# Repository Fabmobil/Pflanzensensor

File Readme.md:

#  Pflanzensensor

Dies ist das Repository mit dem Quellcode und allen Informationen zum Fabmobil Pflanzensensor. Weiterführende Erklärungen sind im [Wiki](https://github.com/Fabmobil/Pflanzensensor/wiki) zu finden.

**Firmware flashen ohne Programmierumgebung:** im Browser per USB über den
[Webflasher](https://fabmobil.github.io/Pflanzensensor/) (Chrome, Edge oder Opera am Computer).

| Verzeichnis | Inhalt |
| --- | --- |
| [`firmware/`](firmware) | Quellcode der Firmware 3 (PlatformIO, ESP8266 und ESP32), Weboberfläche, Tests – Bauen und Entwickeln siehe [firmware/README.md](firmware/README.md) |
| [`webflasher/`](webflasher) | Seite zum Flashen per USB im Browser (GitHub Pages) |
| [`Dokumentation/`](Dokumentation) | Datenblätter, Schaltpläne, Pinouts, 3D-Modelle, Workshop-Unterlagen |

Im [Wiki](https://github.com/Fabmobil/Pflanzensensor/wiki) gibt es weiterführende Informationen und Anleitungen.

wird gefördert von:

und unterstützt von:

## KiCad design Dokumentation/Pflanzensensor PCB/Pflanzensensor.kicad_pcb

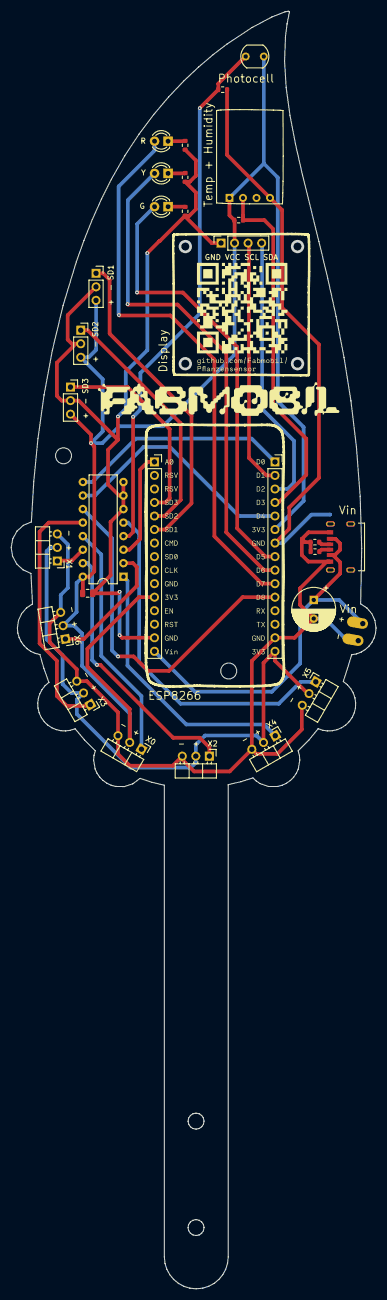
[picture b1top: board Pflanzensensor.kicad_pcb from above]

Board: 2 copper layers, 68.5 x 239.9 mm, 32 parts (0 on the bottom side), 32 nets.

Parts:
+: Conn_01x01; SolderWirePad_1x01_SMD_1x2mm
-: SolderWirePad_1x01_SMD_1x2mm
C1: C_Polarized; CP_Radial_D8.0mm_P3.50mm
C2: 0.1 µF; C_0805_2012Metric
DH1: Conn_01x04; PinSocket_1x04_P2.54mm_Vertical
DHT11: VCC SIG – GND; Aosong_DHT11_5.5x12.0_P2.54mm
ESP1, ESP2: Conn_01x15; PinSocket_1x15_P2.54mm_Vertical
IC1: CD4051B; DIP-16_W7.62mm
LEDG1: Green 568nm; LED_D3.0mm
LEDR1: Red 617nm; LED_D3.0mm
LEDY1: 588nm; LED_D3.0mm
PHR1: R_Photo; R_LDR_5.1x4.3mm_P3.4mm_Vertical
R1: 1KΩ; R_0603_1608Metric
R2: 10KΩ; R_0603_1608Metric
R5, R6: 5K1; R_0603_1608Metric
RG1: 56Ω; R_0603_1608Metric
RR1: 68Ω; R_0603_1608Metric
RY1: 62Ω; R_0603_1608Metric
SD1, SD2, SD3: Conn_01x03; PinSocket_1x03_P2.54mm_Vertical
Vin: GCT_USB4125-GF-A-0190_REVA2
X0, X1, X2, X3, X4, X5, X6: Conn_01x03; PinHeader_1x03_P2.54mm_Horizontal
gndpad: SolderWirePad_1x01_SMD_1x2mm

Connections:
unnamed: +.1, C1.1, ESP1.15 (Vin), Vin.A9, Vin.B9
unnamed: -.1, C1.2, ESP2.14 (GND), R5.2, R6.2, Vin.A12, Vin.B12, X0.3, X1.3, X2.3, X3.3, X4.3, X5.3, X6.3
unnamed: C2.1, DH1.1 (GND), ESP1.14 (GND), IC1.6 (INH), IC1.7 (VEE), IC1.8 (VSS), RG1.2, RR1.2, RY1.2, SD1.2, SD2.2, SD3.2
unnamed: DH1.3 (SCL), ESP2.2 (D1)
unnamed: DH1.4 (SDA), ESP2.3 (D2)
unnamed: C2.2, DH1.2 (VCC), DHT11.1 (VCC), ESP1.11 (3V3), ESP2.6 (GND), IC1.16 (VDD), PHR1.1, R2.1, SD1.3, SD2.3, SD3.3, X0.2, X6.2
unnamed: DHT11.4 (GND), ESP2.7 (3V3), R1.1, gndpad.1
unnamed: DHT11.2 (IO), ESP2.4 (D3), R2.2
unnamed: ESP1.1 (A0), IC1.3 (X)
unnamed: ESP1.6 (SD1), SD1.1
unnamed: ESP1.5 (SD2), SD2.1
unnamed: ESP1.4 (SD3), SD3.1
unnamed: ESP2.1 (D0), IC1.9 (C)
unnamed: ESP2.5 (D4), IC1.10 (B)
unnamed: ESP2.8 (D5), LEDG1.2 (A)
unnamed: ESP2.9 (D6), LEDY1.2 (A)
unnamed: ESP2.10 (D7), LEDR1.2 (A)
unnamed: ESP2.11 (D8), IC1.11 (A)
unnamed: IC1.13 (X0), X0.1
unnamed: IC1.14 (X1), X1.1
unnamed: IC1.15 (X2), X2.1
unnamed: IC1.12 (X3), X3.1
unnamed: IC1.1 (X4), X4.1
unnamed: IC1.5 (X5), X5.1
unnamed: IC1.2 (X6), X6.1
unnamed: IC1.4 (X7), PHR1.2, R1.2
unnamed: ESP2.15 (3V3), X1.2, X2.2, X3.2, X4.2, X5.2
unnamed: LEDG1.1 (K), RG1.1
unnamed: LEDR1.1 (K), RR1.1
unnamed: LEDY1.1 (K), RY1.1
unnamed: R5.1, Vin.A5
unnamed: R6.1, Vin.B5

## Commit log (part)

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2024-08-11 Debugausgabe umgebaut
2024-08-11 Variablenreset gefixt.
2024-08-12 Webhook mit Ping aller X Stunden
2024-08-12 Refactoting
2024-08-12 bugfix
2024-08-12 Version 0.6
2024-08-12 Verbesserung am CSS
2024-08-12 Kommentierung verbessert.
2024-08-12 Anpassen der Reihenfolge der Schwellwerte auf der Adminseite
2024-08-13 Refactoring LEDAmpel Modul
2024-08-14 Produktiondaten + Doku Pflanzensensor_V3
    Die Files aus den Ordnern Assembly und Gerber sind die Produktionsdaten inkl. Stückliste, die der Hersteller für die 100 Stück Bestellung bekommen hat. Die Kicad File ist der aktuelle Stand (August 2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
2024-08-19 passende make.com Vorlagen für neue WebhookSendeInit()-Funktion
2024-08-19 Bugfix für Neustartcount bei WebhookInit
2024-08-21 Update Webhook Logik
2024-08-21 Version bump 0.7
2024-08-24 Debug wird nicht mehr gebraucht
2024-08-24 Bilder verbessert
2024-08-24 Bugfix Filename
2024-09-04 Analogmesswerte in Adminseite angezeigt; Typos gefixt
2024-09-09 Wifi Accesspoint Passwoerter in passwoerter_Beispiel.h statt Configuration.h
2024-09-09 Umbenennung Configuration.h -> einstellungen.h
2024-09-20 Handout für den 3 Tage Workshop
2024-09-20 eindeutigere Bezeichnung der Minimal- und Maximalwerte der Analgosensoren
2024-09-20 bessere Ausgabe auf serieller Schnittstelle bei nicht funktionierendem Sensor
2024-09-20 Sensor wechselt zu Accesspoint-Modus wenn WIFI Verbindung verloren ist. Nicht aktive Wifidaten sind auf der Adminseite editierbar.
2024-09-20 LED Ampel in Modus 1 aus, wenn kein Sensorwert auf Display angezeigt wird.
2024-09-20 weirder bugfix: DHT_H als Variablenname macht Kompilierfehler.
2024-09-20 LED Ampel auf richtigem Weg ausschalten..
2024-09-20 refactoring von displayanzeige; unnötige variablen entfernt; Versionsbump v1.1.1
2024-09-20 Umschalter für AP und WLAN Modus
2024-09-21 AP settings in Admininterface änderbar
2024-09-21 Versionbump 1.2.0
2024-09-21 Versionbump v1.2.1
2024-09-23 Dateien an dieser Stelle nicht mehr benötigt
2024-09-24 Dokuupdate: Handout 3 Tage
2024-09-30 kein Alert bei deaktiviertem Webhook-Modul auf der Adminseite
2024-09-30 Webhook checkbox wird jetzt auch abgefragt.
2024-09-30 Versionbump V1.2.2
2024-10-03 Adminseite, Variablenspeicher und Bugfixes
2024-10-14 logger statt Serial.print
2024-10-19 mehr Umstrukturierungen
2024-10-19 Versionbump auf 1.3.0
2024-10-20 char statt String: siehe notizen.txt
2024-10-20 Umbenennung der Datei
2024-10-20 bugffix
2024-10-20 wir sparen immer noch ram
2024-10-21 F-Strings zum RAM sparen
2024-10-21 Jedes Byte RAM zählt!
2024-10-21 Logger verbraucht jetzt weniger RAM
2024-10-21 Bugfix für Anzeige der SSIDs
2024-10-21 update Stylesheet
2024-10-21 Versionbump v1.3.1
2024-10-21 Versionbump v1.3.2
2024-10-22 Update Workshopanleitungen
2024-10-22 apAktiv hat gefehlt
2024-10-22 Keine Passwoerter auf DEBUG Seite
2024-10-22 Mehr überarbeitung für Wechsel des WLAN Modus
2024-10-22 Workshopdateien hinzugefügt
2024-10-22 Versionbump v1.3.3
2024-10-22 noch mehr Bugfixes
2024-10-23 housekeeping Skripte
2024-10-23 Die Dateien sollten nie im Repo landen
2024-10-23 gitignore update
2024-10-23 step 1: sensorklasse
2024-10-24 immer akutelle libraries
2024-10-24 update HousekeepingSkripte
2024-10-24 Checkboxüberprüfung überarbeitet
2024-10-24 Versionsbump v1.3.4
2024-11-04 Typo
2024-11-04 labels für ports
2025-09-15 Erste Version der Mailsendefunktion
2025-09-15 added todo
2025-10-15 new ui
2025-10-15 css Vereinfachung
2025-10-15 Logo kleiner
2025-10-15 Version 2.19.0: Neues Admininterface
2025-10-17 Version 2.21.0: Mehr UI Updates, mehr AJAX
2025-10-17 Version 2.22.1: CSS Anpassungen und kleinere Fixes
2025-10-19 Version 2.23.1: kleine Bugfixes und Übersetzungen
2025-10-19 V2.23.3: Min Max Anzeige bei Threshold Slider
2025-10-21 Aufräumen
2025-10-22 V2.24.0: Autocal für Analogsensoren
2025-10-22 clang format über alles
2025-10-22 V2.24.2: fix Display Settings bug
2025-10-22 V2.24.3: Kleinere Bugfixes
2025-10-22 V2.24.5: Aufräumen
2025-10-22 Bugfix Display Sensor
2025-10-22 Update der Dokumentation
2025-10-22 Bild vom Webinterface
2025-10-23 MD5 für Update deaktiviert
2025-10-23 Revise sponsorship section in Readme.md
    Updated sponsorship section with logos and links.
2025-10-23 Initial plan
2025-10-23 Add PreferencesManager class implementation
2025-10-27 Kurzvortrag Mikrocontroller
2025-10-28 Update Dokumentation
2025-11-03 Add Preferences library and refactor configuration persistence
    - Added Preferences library to platformio.ini
    - Created preferences_manager.h/.cpp with namespace-based configuration storage
    - Implemented helper functions for all configuration namespaces (general, WiFi, display, log, LED traffic light, debug, sensors)
    - Updated manager_config_persistence.cpp to use Preferences as primary storage
    - Added migration logic from JSON to Preferences with backup
    - Updated loadFromFile to check Preferences first, then migrate from JSON if needed
2025-11-03 Update DisplayManager to use Preferences for display settings
    - Modified loadConfig() to check Preferences first, then migrate from JSON
    - Modified saveConfig() to write to Preferences
    - Added migration logic from display_config.json to Preferences with backup
    - Sensor-specific display settings kept in separate JSON file for now
    - Added comprehensive German logger messages for display operations
2025-11-03 Final verification and summary of Preferences refactoring
2025-11-03 Update documentation to clarify Preferences storage and current state
    - Documented that Preferences are stored in EEPROM (0x405FB000), separate from LittleFS
    - Clarified that Preferences survive filesystem flashes
    - Listed what is currently in Preferences vs still in JSON (sensors.json)
    - Removed references to automatic JSON migration
    - Noted that analog sensor raw values and autocal settings are NOT yet in Preferences
    - Updated README to reflect current implementation state
2025-11-03 Update sensor atomic update functions to use Preferences (partial)
    - Updated updateSensorThresholdsInternal to use Preferences
    - Updated updateAnalogMinMaxInteger to use Preferences
    - Updated updateAnalogMinMaxIntegerNoReload to use Preferences (no reload)
    - Removed JSON file operations from these functions
    - All atomic updates now write directly to sensor namespace in Preferences
    Still need to update:
2025-11-04 Update documentation with EEPROM space strategy
    - Clarified that only runtime-modifiable data stored in Preferences (~3.3KB)
    - Static metadata (names, units, fieldNames) defined in code
    - Updated sensor namespace documentation with example
    - Removed references to JSON storage for sensors
    - Documented what is and isn't stored to fit 4KB EEPROM limit
2025-11-04 Remove all old JSON code from sensor persistence
    - Removed unused applySensorSettingsFromJson() function (277 lines)
    - Removed ArduinoJson includes from manager_sensor_persistence.cpp
    - Removed static JsonDocument declaration
    - Removed applySensorSettingsFromJson declaration from headers
    - Updated updateAnalogMinMaxInteger() to use Preferences instead of JSON
    - Updated updateAnalogMinMaxIntegerNoReload() to use Preferences instead of JSON
2025-11-04 Fix compilation error: rename DISPLAY to DISP to avoid Arduino.h macro conflict
    - Renamed PreferencesNamespaces::DISPLAY to PreferencesNamespaces::DISP
    - Updated all references in preferences_manager.cpp and manager_display.cpp
    - Resolves conflict with Arduino.h's #define DISPLAY 0x1 macro
    - Namespace string remains "display" (no functional change)
2025-11-04 Kompilierfehler behoben
2025-11-04 Remove obsolete JSON file download/upload functionality
    - Removed handleDownloadConfig() - config no longer stored in JSON file (125 lines)
    - Removed handleDownloadSensors() - sensors no longer stored in JSON file (42 lines)
    - Removed handleUploadConfig() - JSON upload no longer needed with Preferences (130 lines)
    - Removed route registrations for /admin/downloadConfig, /admin/downloadSensors, /admin/uploadConfig
    - Removed download/upload UI buttons from admin page (admin_handler_cards.cpp)
    - Removed download buttons from update/OTA page (web_ota_handler.cpp)
2025-11-05 Implement atomic Preferences updates for individual config changes
    - Added atomic update methods to PreferencesManager for each config type:
    - updateDeviceName(), updateAdminPassword(), updateMD5Verification()
    - updateFileLoggingEnabled(), updateWiFiCredentials()
    - updateLedTrafficMode(), updateLedTrafficMeasurement()
    - updateDebugRAM(), updateDebugMeasurementCycle(), updateDebugSensor()
    - updateDebugDisplay(), updateDebugWebSocket()
2025-11-05 Fix compilation errors: add missing error enum values
    - Added SAVE_FAILED to DisplayError enum
    - Changed ConfigError::INVALID_INPUT to ConfigError::VALIDATION_ERROR
    - Fixes compilation errors in preferences_manager.cpp and manager_display.cpp
2025-11-05 Remove old display-specific routes and mark deprecated code
2025-11-05 Move preferences_manager to manager_config_preferences for consistency
2025-11-05 Fix WiFi settings atomic save (remove full config save)
2025-11-05 small Bugfix
2025-11-05 Remove redundant logging and fix toast messages to show friendly names
2025-11-05 Refactor ConfigManager to use DRY helpers - reduce code bloat
2025-11-05 Remove unnecessary wrapper methods - use generic update helpers directly
2025-11-05 Fix compilation errors - remove duplicate setDeviceName and update DisplayManager
2025-11-05 Fix Arduino.h DISPLAY macro conflict - use DISP namespace
2025-11-05 Kein default JSON generator mehr + Bugfixes
2025-11-05 Complete OTA sensor settings backup/restore implementation
2025-11-05 Begin EEPROM-based storage to replace Preferences library
2025-11-05 Add comprehensive documentation for EEPROM-based configuration storage
2025-11-05 Fix function signatures in manager_config_preferences.cpp
2025-11-05 Bugfixes
2025-11-05 Increase EEPROM namespace size to fix sensor data storage
2025-11-05 Use separate WiFi namespaces and add debug logging for EEPROM writes
2025-11-05 Revert EEPROM changes and implement LittleFS-based config with OTA backup/restore
2025-11-05 Fix WiFi settings persistence and analog inversion by using unified setConfigValue
2025-11-05 Fix web_ota_handler to use separate WiFi namespaces (wifi1, wifi2, wifi3)
2025-11-05 fix for Wifi settings storage
2025-11-06 Remove flawed RAM-based backup, use only file-based backup for all settings
2025-11-06 Fix missing command variable in handleUpdateUpload
2025-11-06 Add _backupFileContent member and use isEmpty() check
2025-11-06 Implement dual LittleFS partition system (Phase 1 & 2 partial)
2025-11-06 Remove backup/restore functions - no longer needed with dual partitions
2025-11-06 Update remaining file operations to use MainFS (logger, admin, display)
2025-11-06 Add comprehensive Copilot coding agent instructions
2025-11-06 Implement flash-based configuration persistence for OTA filesystem updates
    - Revert dual LittleFS partition approach (not supported on ESP8266)
    - Add FlashPersistence module to store config in firmware flash area
    - Config stored beyond compiled code using ESP.getSketchSize() + safety margin
    - Survives filesystem OTA updates (firmware partition untouched)
    - Integrate with ConfigPersistence save/restore workflow
    - Update OTA handler to restore from flash instead of LittleFS file
2025-11-06 some bugfixes
2025-11-07 web handler caching; einige Logübersetzungen; MinMax Werte nur 1x die Minute persistiert
2025-11-07 Sensorname ändern mit eigener Methode; Schönes JSON als Configdownload
2025-11-09 Funktioniert nun endlich
2025-11-09 Readme wiederhergestellt
2025-11-11 Debuglogsettings ändern geht auch ohne Auth jetzt
